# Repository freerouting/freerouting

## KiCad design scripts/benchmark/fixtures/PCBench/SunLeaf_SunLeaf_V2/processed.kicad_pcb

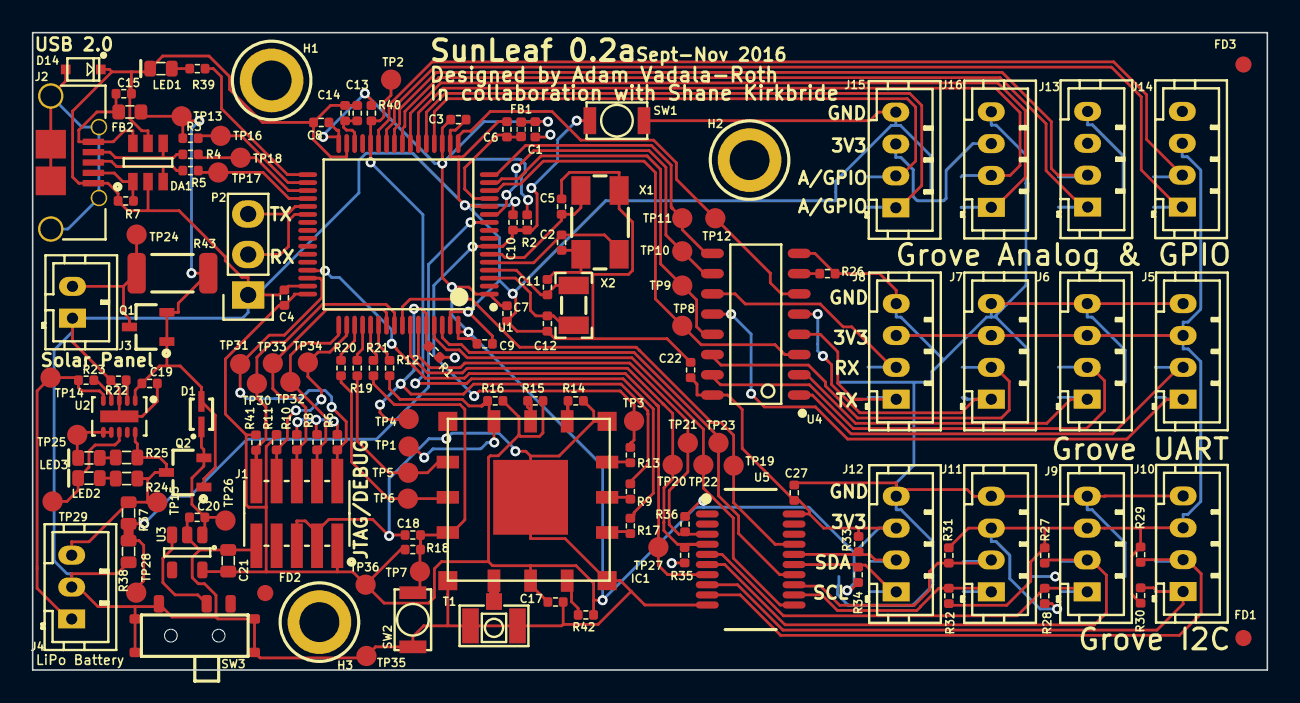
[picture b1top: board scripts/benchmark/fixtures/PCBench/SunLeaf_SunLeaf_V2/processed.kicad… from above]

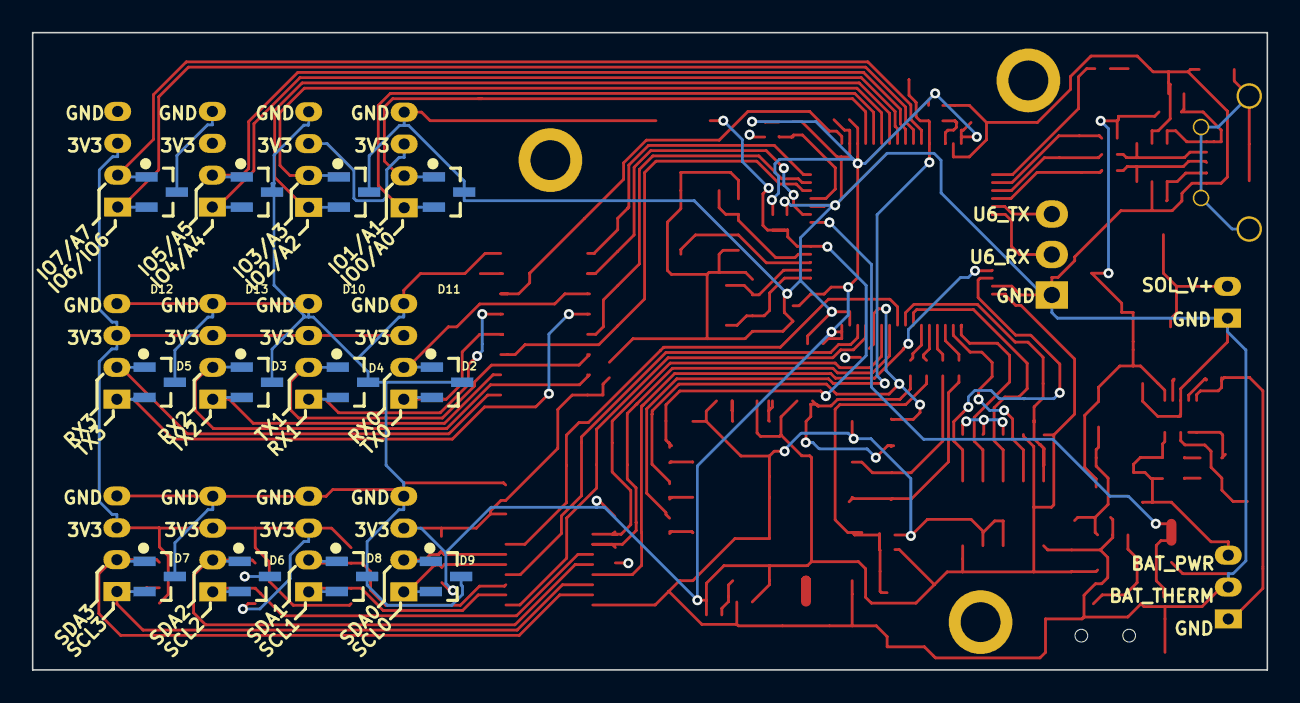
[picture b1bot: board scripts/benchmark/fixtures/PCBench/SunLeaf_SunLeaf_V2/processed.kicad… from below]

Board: 4 copper layers, 77.5 x 40.0 mm, 158 parts (12 on the bottom side), 92 nets.

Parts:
C1, C3, C4, C6, C7, C8, C9, C10, C14, C15, C17, C18, C22, C27: CL05B104JP5NNNC; C0402
C2, C5: CL05C090CB5NNNC; C0402
C11, C12: CL05C180GB5NCNC; C0402
C13: CL05A475KQ5NRNC; C0402
C19, C20: CL05A105KA5NQNC; C0402
C21: CL10A106KQ8NNNC; C0603
D1: BAT20JFILM
D2, D3, D4, D5, D6, D7, D8, D9, D10, D11, D12, D13: PESD3V3L2BT,215
D14: RSB39VTE-17
DA1: ESDA6V1BC6
FB1: BLM15HG601SN1D
FB2: MI0603K300R-10
FD1, FD2, FD3: FIDUCIAL
H1, H2, H3: M2.5_Hole; M2.5_HOLE
IC1: ESP_09; ESP-09
J1: 20021121-00010C4LF
J2: 0475890001-MicroUSBPort; 0475890001
J3: B2B-PH-K-S(LF)(SN)
J4: B3B-PH-K-S(LF)(SN)
J5, J6, J7, J8, J9, J10, J11, J12, J13, J14, J15, J16: B4B-PH-K-S(LF)(SN)
LED1: LTST-C193TBKT-5A; LED0603
LED2: LTST-C191KGKT; LED0603
LED3: LTST-C191KFKT; LED0603
P2: CONN_01X03; Pin_Header_Straight_1x03
Q1, Q2: DMG2307L-7
R1, R3, R14, R15, R16, R40, R42: RC1005F103CS; R0402
R2, R6, R8, R10, R11, R18, R23, R26, R39, R41: RC1005F102CS; R0402
R4, R5: CPF0402B22RE1; R0402
R7: RC1005J473CS; R0402
R9, R12, R13, R17, R19, R20, R21: RC1005F201CS; R0402
R22: RC1005F4870CS; R0402
R24, R25: RC1608J202CS; R0603
R27, R28, R29, R30, R31, R32, R33, R34, R35, R36: RC1005F472CS; R0402
R37, R38: ERA-3AEB3741V; R0603
R43: RC5025J000CS; R2010
SW1, SW2: B3U-1000P
SW3: CUS-12TB
T1: 1909763-1
TP1, TP2, TP3, TP4, TP5, TP6, TP7, TP8, TP9, TP10, TP11, TP12, TP13, TP14, TP15, TP16, TP17, TP18, TP19, TP20, TP21, TP22, TP23, TP24, TP25, TP26, TP27, TP28, TP29, TP30, TP31, TP32, TP33, TP34, TP35, TP36: TEST_POINT
U1: STM32F446RET6_-_TQFP64; STM32F446RET6
U2: BQ24210DQCT; BQ24210
U3: AP2112K-3.3TRG1
U4: 74HC4052D
U5: PCA9518DBQR
X1: ABM3B8.000MHZB2T
X2: ABS07-32.768KHZ-9-T

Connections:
+3V3: C1.1, C3.1, C4.1, C7.1, C8.1, C9.1, C17.1, C21.1, C22.1, C27.1, FB1.1, IC1.15, J1.1, J5.3, J6.3, J7.3, J8.3, J9.3, J10.3, J11.3, J12.3, J13.3, J14.3, J15.3, J16.3, R2.1, R6.1, R8.1, R10.1, R11.1, R15.1, R16.1, R18.1, R27.1, R28.1, R29.1, R30.1, R31.1, R32.1, R33.1, R34.1, R35.1, R36.1, R40.1, R41.1, R42.2, TP36.1, U1.1, U1.19, U1.32, U1.48, U1.64, U3.5, U4.16, U5.20
/Analog and Digital Grove IO/ANIO_0: D13.1, J13.2, U1.25
/Analog and Digital Grove IO/ANIO_1: D13.2, J13.1, U1.24
/Analog and Digital Grove IO/ANIO_2: D12.1, J14.2, U1.27
/Analog and Digital Grove IO/ANIO_3: D12.2, J14.1, U1.26
/Analog and Digital Grove IO/ANIO_4: D11.1, J15.2, U1.20
/Analog and Digital Grove IO/ANIO_5: D11.2, J15.1, U1.21
/Analog and Digital Grove IO/ANIO_6: D10.1, J16.2, U1.22
/Analog and Digital Grove IO/ANIO_7: D10.2, J16.1, U1.23
/I2C Grove Sensors/EN1_IMUX: TP27.1, U1.45, U5.7
/I2C Grove Sensors/EN2_IMUX: TP22.1, U1.61, U5.11
/I2C Grove Sensors/EN3_IMUX: TP23.1, U1.62, U5.14
/I2C Grove Sensors/EN4_IMUX: TP19.1, U1.57, U5.17
/I2C Grove Sensors/I2C_SCL: R35.2, TP20.1, U1.58, U5.4
/I2C Grove Sensors/I2C_SDA: R36.2, TP21.1, U1.59, U5.3
/MCU-STM32F446RET6/BAT_VOLT: R37.2, R38.1, TP28.1, U1.10
/MCU-STM32F446RET6/ESPTOST_BOOT0: R1.1, R9.1, TP4.1, U1.60
/MCU-STM32F446RET6/ESPTOST_BOOT1: R17.1, R40.2, TP2.1, U1.28
/MCU-STM32F446RET6/ESP_PGM_MODE: R12.1, U1.54
/MCU-STM32F446RET6/ESP_ST_RST: C10.1, R2.2, R13.1, SW1.1, TP3.1, U1.7
/MCU-STM32F446RET6/ESP_URX: R19.2, U1.52
/MCU-STM32F446RET6/ESP_UTX: R20.2, U1.51
/MCU-STM32F446RET6/HEARTBEAT: R39.1, U1.33
/MCU-STM32F446RET6/NJTRST: J1.10, R41.2, TP30.1, U1.56
/MCU-STM32F446RET6/STM_ESP_RST: R21.2, U1.53
/MCU-STM32F446RET6/SWCLK_TCK: J1.4, R8.2, TP32.1, U1.49
/MCU-STM32F446RET6/SWDIO_TMS: J1.2, R6.2, TP31.1, U1.46
/MCU-STM32F446RET6/SWO_TDI: J1.8, R11.2, TP34.1, U1.50
/MCU-STM32F446RET6/SWO_TDO: J1.6, R10.2, TP33.1, U1.55
/MCU-STM32F446RET6/UART6_RX: P2.2, U1.38
/MCU-STM32F446RET6/UART6_TX: P2.3, U1.37
/MCU-STM32F446RET6/UART_S_RX: TP9.1, U1.15, U4.13
/MCU-STM32F446RET6/USW_EN: TP12.1, U1.17, U4.6
/MCU-STM32F446RET6/USW_S0: TP10.1, U1.11, U4.10
/MCU-STM32F446RET6/USW_S1: TP11.1, U1.16, U4.9
/MCU-STM32F446RET6/VBUS: C19.1, D1.1, FB2.1, Q1.1, Q1.2, Q2.1, R3.2, R43.2, TP13.1, U2.1
/Power-System/BAT: J4.3, Q2.3, R24.2, R25.2, R37.1, TP15.1, U2.10
/Power-System/THERM: J4.1, R23.2, TP14.1, U2.5
/UART Grove Sensors/UART_RX0: D5.1, J5.2, U4.1
/UART Grove Sensors/UART_RX1: D4.1, J6.2, U4.14
/UART Grove Sensors/UART_RX2: D3.1, J7.2, U4.15
/UART Grove Sensors/UART_RX3: D2.1, J8.2, U4.11
/UART Grove Sensors/UART_S_RX: TP8.1, U1.14, U4.3
/UART Grove Sensors/UART_TX0: D5.2, J5.1, U4.12
/UART Grove Sensors/UART_TX1: D4.2, J6.1, U4.5
/UART Grove Sensors/UART_TX2: D3.2, J7.1, U4.2
/UART Grove Sensors/UART_TX3: D2.2, J8.1, U4.4
/WiFi-ESP8266-ESP-09/ANTENNA: IC1.14, T1.1
/WiFi-ESP8266-ESP-09/PGM_MODE: IC1.8, R12.2, R16.2, TP1.1
GND: C1.2, C2.2, C3.2, C4.2, C5.2, C6.2, C7.2, C8.2, C9.2, C10.2, C11.2, C12.2, C13.2, C14.2, C15.1, C17.2, C18.2, C19.2, C20.2, C21.2, C22.2, C27.2, D2.3, D3.3, D4.3, D5.3, D7.3, D8.3, D9.3, D10.3, D11.3, D12.3, D13.3, D14.2, DA1.2, DA1.5, IC1.1, IC1.5, IC1.9, IC1.13, IC1.17, J1.3, J1.5, J1.9, J2.5, J3.1, J4.2, J5.4, J6.4, J7.4, J8.4, J9.4, J10.4, J11.4, J12.4, J13.4, J14.4, J15.4, J16.4, LED1.2, P2.1, R1.2, R7.2, R14.2, R22.2, R26.1, R38.2, SW1.2, SW2.2, SW3.1, SW3.4, T1.2, TP35.1, U1.12, U1.18, U1.31, U1.47, U1.63, U2.3, U2.11, U3.2, U4.8, U5.10, X1.2, X1.4
unnamed: C2.1, U1.5, X1.1
unnamed: C5.1, U1.6, X1.3
unnamed: C6.1, FB1.2, U1.13
unnamed: C11.1, U1.4, X2.1
unnamed: C12.1, U1.3, X2.2
unnamed: C13.1, C14.1, U1.30
unnamed: C15.2, DA1.6, FB2.2, J2.1
unnamed: C18.1, IC1.12, R18.2, R21.1, SW2.1, TP7.1
unnamed: C20.1, D1.2, Q2.2, TP26.1, U3.1
unnamed: D6.1, J9.2, R27.2, U5.6
unnamed: D6.2, J9.1, R28.2, U5.5
unnamed: D7.1, J10.2, R29.2, U5.9
unnamed: D7.2, J10.1, R30.2, U5.8
unnamed: D8.1, J11.2, R31.2, U5.13
unnamed: D8.2, J11.1, R32.2, U5.12
unnamed: D9.1, J12.2, R33.2, U5.16
unnamed: D9.2, J12.1, R34.2, U5.15
unnamed: D14.1, J2.6, J2.7, J2.8, J2.9, J2.10, J2.11
unnamed: DA1.1, J2.4, R7.1
unnamed: DA1.3, J2.3, R5.2
unnamed: DA1.4, J2.2, R4.2
unnamed: IC1.2, R17.2
unnamed: IC1.3, R9.2
unnamed: IC1.4, R13.2
unnamed: IC1.6, R14.1
unnamed: IC1.7, R15.2
unnamed: IC1.10, R19.1, TP5.1
unnamed: IC1.11, R20.1, TP6.1
unnamed: IC1.16, R42.1
unnamed: J3.2, Q1.3, R43.1, TP24.1
unnamed: LED1.1, R39.2
unnamed: LED2.1, R24.1
unnamed: LED2.2, TP29.1, U2.8
unnamed: LED3.1, R25.1
unnamed: LED3.2, TP25.1, U2.6, U2.7
unnamed: R3.1, TP16.1, U1.34
unnamed: R4.1, TP18.1, U1.35
unnamed: R5.1, TP17.1, U1.36
unnamed: R22.1, U2.2
unnamed: R23.1, U2.4
unnamed: R26.2, U4.7
unnamed: SW3.2, U3.3

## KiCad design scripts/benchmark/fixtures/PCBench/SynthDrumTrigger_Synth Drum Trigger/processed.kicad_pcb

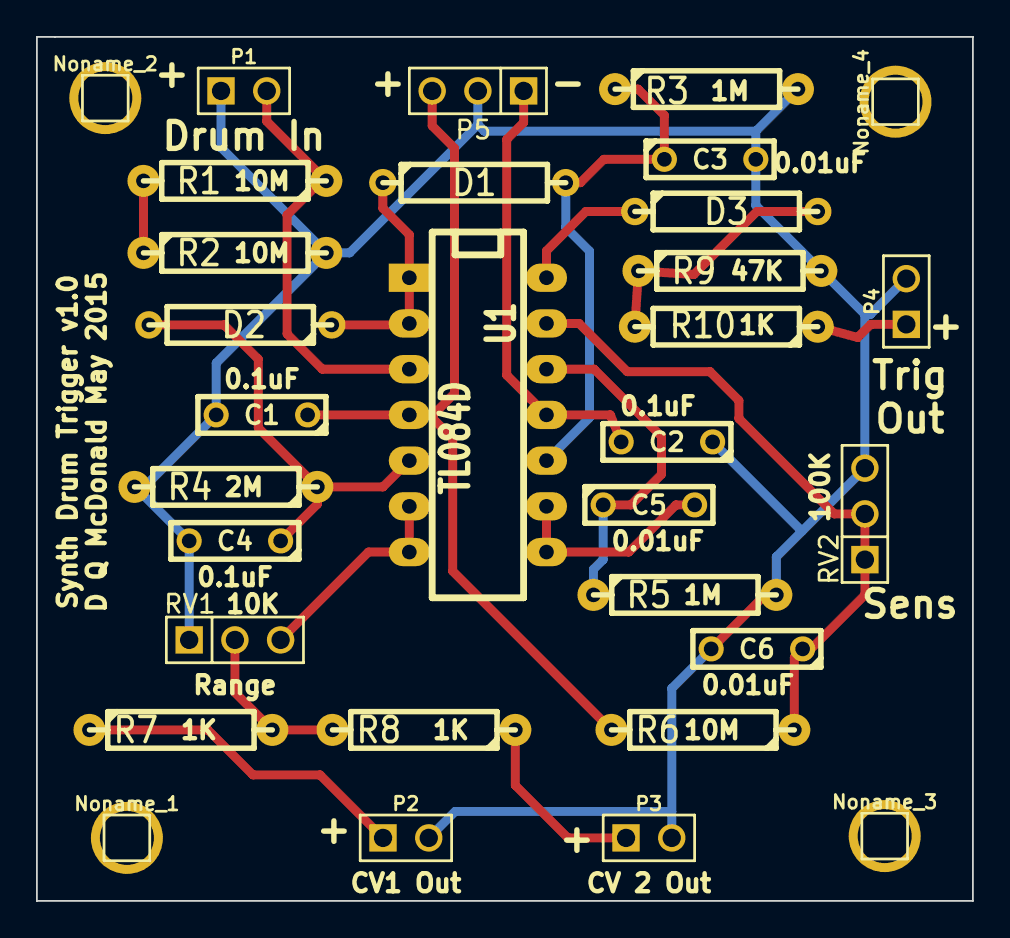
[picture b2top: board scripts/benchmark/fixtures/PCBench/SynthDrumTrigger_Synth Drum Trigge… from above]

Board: 2 copper layers, 52.0 x 48.0 mm, 31 parts (0 on the bottom side), 18 nets.

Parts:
C1, C2, C4: 0.1uF; C2
C3, C6: 0.01uF; C2
C5: 0.01; C2
D1, D2, D3: DIODE; R4
Noname_1, Noname_2, Noname_3, Noname_4: Val**; PIN_ARRAY_1
P1, P2, P3, P4: CONN_2; PIN_ARRAY_2X1
P5: Power_In; PIN_ARRAY_3X1
R1, R2, R6: 10M; R4-LARGE_PADS
R3, R5: 1M; R4-LARGE_PADS
R4: 2M; R4-LARGE_PADS
R7, R8, R10: 1K; R4-LARGE_PADS
R9: 47K; R4-LARGE_PADS
RV1: 10K; PIN_ARRAY_3X1
RV2: 100K; PIN_ARRAY_3X1
U1: TL084D; DIP-14__300_ELL

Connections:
+12V: C1.1, P5.3, R6.2, U1.4
-12V: C2.2, P5.1, U1.11
GND: C1.2, C2.1, C3.2, C4.2, C6.2, P1.1, P2.2, P3.2, P4.2, P5.2, R2.2, R3.2, R4.2, R5.2, R9.2, RV1.1, RV2.3
unnamed: C3.1, D1.2, R3.1, U1.10
unnamed: C4.1, D2.2, R4.1, U1.5
unnamed: C5.1, R5.1, U1.12
unnamed: C5.2, U1.8, U1.9
unnamed: C6.1, R6.1, RV2.1, RV2.2, U1.13
unnamed: D1.1, D2.1, U1.1, U1.2
unnamed: D3.1, U1.14
unnamed: D3.2, R9.1, R10.2
unnamed: P1.2, R1.1, U1.3
unnamed: P2.1, R7.1
unnamed: P3.1, R8.1
unnamed: P4.1, R10.1
unnamed: R1.2, R2.1
unnamed: R7.2, R8.2, RV1.2
unnamed: RV1.3, U1.6, U1.7

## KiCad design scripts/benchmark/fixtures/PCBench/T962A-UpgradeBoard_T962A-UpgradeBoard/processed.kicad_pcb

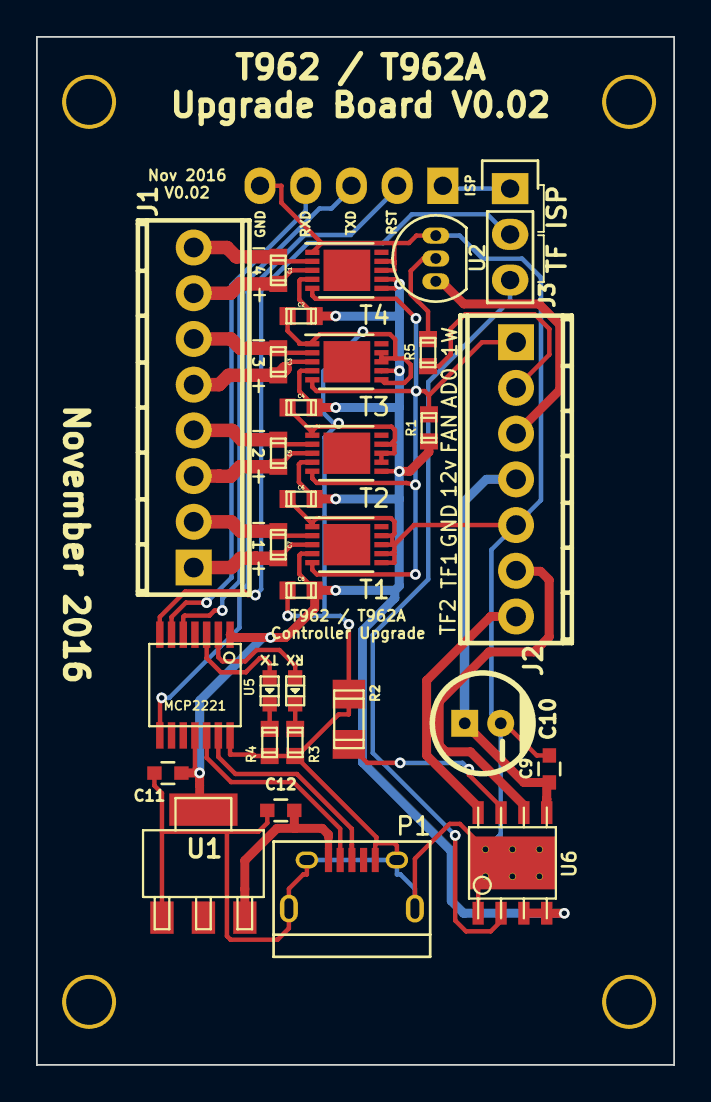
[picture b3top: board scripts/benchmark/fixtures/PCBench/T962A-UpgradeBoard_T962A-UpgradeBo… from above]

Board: 2 copper layers, 35.4 x 57.1 mm, 32 parts (1 on the bottom side), 31 nets.

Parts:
C1, C3, C5, C7: 10nF; c_0603
C2, C4, C6, C8: 100nF; c_0603
C9: 0.1uF; C_0603
C10: 47uF; CP_5x11mm
C11, C12: 10uF; C_0603
J1: HEADER_8; mpt_0,5%2f8-2,54
J2: HEADER_7; mpt_0,5%2f7-2,54
J3: ISP Jumper; Pin_Header_Straight_1x03
LD1, LD2: LED; Led_0603
P1: USB_OTG; USB_Micro-B
P2: CONN_01X05; Pin_Header_Straight_1x05
R1, R5: 4K7; r_0603
R2: 0R; r_1206
R3, R4: 400; r_0603
T1, T2, T3, T4: MAX31850; MAX31850_MAX31851_TDFN_EP
U1: LDO_REG; sot223
U2: Transistor; TO-92_Inline_Narrow_Oval
U5: MCP2221; tssop-14
U6: DRV8870; HSOP-8

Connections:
1W: J2.1, R1.2, T1.5, T2.5, T3.5, T4.5
5V: C12.1, P1.1, U1.3
12V: C9.1, C10.1, J2.4, U6.5
AD0: J2.2, R5.1
D+: P1.3, U5.13
D-: P1.2, U5.12
FAN1: J2.3, U2.1
GND: C2.2, C4.2, C6.2, C8.2, C9.2, C10.2, C11.2, C12.2, J2.5, P1.5, P1.6, P2.5, R2.2, R3.1, R4.1, T1.1, T1.6, T1.7, T1.8, T1.9, T2.1, T2.7, T2.8, T2.9, T3.1, T3.6, T3.8, T3.9, T4.1, T4.8, T4.9, U1.1, U2.3, U5.14, U6.1, U6.9
GP2: J3.2, U5.7
INT2: J3.3, U6.2
LEDRX: LD1.1, U5.2
LEDTX: LD2.1, U5.3
unnamed: LD1.2, R3.2
unnamed: LD2.2, R4.2
unnamed: R2.1, U6.7
unnamed: R5.2, U2.2
OUT1: J2.6, U6.6
OUT2: J2.7, U6.8
RXD0: P2.4, U5.6
T1+: C7.1, J1.1, T1.3
T1-: C7.2, J1.2, T1.2
T2+: C5.1, J1.3, T2.3
T2-: C5.2, J1.4, T2.2
T3+: C3.1, J1.5, T3.3
T3-: C3.2, J1.6, T3.2
T4+: C1.1, J1.7, T4.3
T4-: C1.2, J1.8, T4.2
TXD0: P2.3, U5.5
VCC: C2.1, C4.1, C6.1, C8.1, C11.1, R1.1, T1.4, T2.4, T2.6, T3.4, T3.7, T4.4, T4.6, T4.7, U1.2, U5.1, U5.11, U6.3, U6.4
n_ISP: J3.1, P2.1
n_RESET: P2.2, U5.8
